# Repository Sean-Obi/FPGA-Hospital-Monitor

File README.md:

# FPGA Hospital Monitor

A three-channel patient monitor built on an FPGA: **ECG and heart rate**,
**blood oxygen (SpO₂)** and **skin temperature**, shown on a hospital-style
display.

The sensors are bought modules. Everything after them — the ADC control,
the I²C bus master, filtering, baseline removal, beat detection, the
heart-rate divider, the ratio-of-ratios oximetry maths, temperature
conversion, and the serial link — is Verilog running on a Digilent
Cmod A7-35T. The laptop only draws what it is sent.

The beat detector is scored against cardiologist annotations from the
PhysioNet MIT-BIH Arrhythmia Database, so its accuracy is a measured figure
rather than an impression.

> **Not a medical device.** Hobby and education only. Do not use it for
> diagnosis or treatment.

---

## The signal chain

```
 electrodes          fingertip             skin
     |                   |                   |
  AD8232             MAX30102              TMP36
  amp + filters      red + IR LEDs,        10 mV / °C
  (bought)           18-bit ADC (bought)   (bought)
     |                   |                   |
     |                   |             op-amp buffer     <- needed, see Wiring
     |                   |                   |
     v                   v                   v
   XADC VAUX4         I²C bus             XADC VAUX12
     |                   |                   |
 xadc_reader       i2c_master           xadc_reader
 (2 channels,      max30102_driver      (same block)
  sequencer)           |                     |
     |             spo2_calc             temp_convert
     |             udiv (44-bit)             |
     |                   |                   |
 ecg_filter              |                   |
 baseline_remove         |                   |
 beat_detect             |                   |
 bpm_calc / bpm_div      |                   |
     |                   |                   |
     +-------------------+-------------------+
                         |
                  telemetry_uart        S/B/T/O messages, 115200 baud
                         |
                  scripts/ecg_monitor.py --port COMx
```

`buzzer` and `led_flash` hang off the `beat` pulse.

---

## What goes over the serial line

Every message is six characters: a tag, four decimal digits with leading
zeros, newline.

| Message | Meaning | How often |
|---|---|---|
| `S2048` | one raw ECG sample, 0–4095 | 500 / s |
| `B0075` | heart rate, BPM | once per beat |
| `T0345` | skin temperature, tenths of °C (34.5 °C) | 2 / s |
| `O0098` | SpO₂ percent. `O0000` = no finger. `O0999` = MAX30102 not responding | every 2.6 s |

Bandwidth: the sample stream is 500 × 6 × 10 = 30,000 bit/s; the rest is a
few messages a second. About 27 % of the 115,200 baud line.

Measured on hardware: 0 bad lines in 114,000 messages.

---

## Hardware

| Part | Notes |
|---|---|
| Digilent Cmod A7-35T | 48-pin DIP, has the XADC built in |
| AD8232 breakout | ECG front end. Run it at **3.3 V**, not 5 V |
| ECG electrode pads + 3-lead snap cable | the cable plugs into the AD8232's 3.5 mm jack |
| MAX30102 module | pulse oximeter, I²C. **Pull-up jumper must be on 3.3 V** — see below |
| TMP36 | analogue temperature sensor, TO-92 |
| MCP6002 or LM358 | dual op-amp, used as a unity-gain buffer for the TMP36 |
| 0.1 µF capacitor | decoupling for the TMP36 |
| Piezo buzzer (passive) + 100–220 Ω resistor | a piezo draws well under 1 mA, so it runs straight off the FPGA pin |
| Full-size breadboard + male jumpers | the Cmod straddles the centre channel |

### The Cmod A7 pins this design uses

**Only two of the 48 DIP pins are power:** pin 24 (VU) and pin 25 (GND).
There is **no 3.3 V on the DIP header** — it is only on the Pmod socket.
With USB attached the board drives about 4.7 V *out* onto pin 24, which
would damage every sensor here. Power all three from Pmod JA pin 6 (or 12).

DIP pins 15 and 16 each pass through an on-board 2.32 kΩ / 1 kΩ divider,
so they accept **0 to 3.3 V** and present 0 to 1 V to the XADC. One ADC
count is therefore 3.32 V / 4096 = **0.81 mV** at the pin (measured: 4051
counts on the 3.28 V rail). The negative half of each pair (G2, J2) is
grounded on the board, so they are single-ended inputs. With nothing
connected, the 1 kΩ leg holds the pin at 0 V, so an unwired input reads 0.

### Wiring: AD8232 (ECG)

| AD8232 | Cmod A7 |
|---|---|
| 3.3V | Pmod JA pin 6 |
| GND | Pmod JA pin 5, or DIP pin 25 |
| OUTPUT | DIP pin 15 (`xa_p[0]`, package pin G3, VAUX4) |

Electrode cable into the 3.5 mm jack. IEC colours: **red** just below the
right collarbone, **yellow** just below the left collarbone, **green** on the
lower left ribs. On the soft flesh, not on the bone. If the R peak comes
out pointing down, swap red and yellow.

### Wiring: TMP36 (skin temperature) — needs the buffer

The TMP36 can only source **50 µA**. The Cmod's input divider draws about
**250 µA** at the voltages involved, so connected directly the sensor's
output collapses and the reading is garbage. A unity-gain op-amp buffer
in between fixes it: the op-amp copies the voltage and supplies the current.

```
   TMP36 (flat face towards you, legs down):   +Vs   Vout   GND

   +Vs  ─── Pmod JA 3.3 V        (0.1 µF from +Vs to GND, close to the sensor)
   GND  ─── GND
   Vout ─── op-amp IN+ (pin 3)

   MCP6002 / LM358, DIP-8, same pinout for both:
       pin 8  V+   ─── Pmod JA 3.3 V
       pin 4  V−   ─── GND
       pin 3  IN+  ─── TMP36 Vout
       pin 2  IN−  ─── pin 1   (output tied back to the inverting input = gain of 1)
       pin 1  OUT  ─── DIP pin 16  (`xa_p[1]`, package pin H2, VAUX12)
```

Tape the flat face of the TMP36 against skin with something over it to
insulate it from the air. Inner wrist works; armpit reads closer to core.
It reads **skin** temperature, typically 32–35 °C, and is labelled as such
on the display.

### Wiring: MAX30102 (SpO₂)

| MAX30102 | Cmod A7 |
|---|---|
| VIN | Pmod JA 3.3 V |
| GND | GND |
| SCL | DIP pin 2 (`scl`, package pin L3) |
| SDA | DIP pin 3 (`sda`, package pin A16) |
| INT | not used |

**Check the pull-up jumper.** Most of these modules have a three-pad
solder jumper that selects whether the I²C pull-ups go to 1.8 V or 3.3 V.
The FPGA's inputs need 2.0 V to read a logic high, so at 1.8 V nothing
works and nothing explains why. With the module powered, a multimeter from
SCL to GND must read about 3.3 V. If it reads 1.8 V, move the jumper, or
add 4.7 kΩ resistors from SCL and SDA to 3.3 V. The MAX30102's own pins are
rated to 6 V, so 3.3 V pull-ups are fine for it.

Finger on the sensor window, light pressure, keep still. The first reading
takes about 5 s (two 2.56 s blocks).

### Buzzer

DIP pin 1 (`piezo`, package pin M3) → 100–220 Ω → buzzer **+**. Buzzer **−** to GND.

### Safety

Electrodes on your chest is a different risk category from a sensor
clipped on a finger.

- **Unplug the laptop charger while electrodes are attached.** USB to a
  mains-powered laptop puts you indirectly on mains equipment. Laptop on
  battery, board on USB.
- Use proper single-use ECG pads.
- **Do not power the board from batteries on DIP pin 24 while USB is
  connected.** The reference manual is explicit — "if you have a power
  source attached to the VU pin, you must disconnect it before attaching
  a USB host, or risk damaging it." Since USB carries the data, battery
  power is not an option for this project.
- Insert and remove the Cmod with USB unplugged. Nothing is live until
  USB goes in.

---

## The shield PCB (KiCad)

The breadboard works for bring-up, but three sensor modules, an op-amp and
a regulator on jumper wires is fragile and noisy. `hardware/` holds a KiCad
design for a shield the Cmod A7 plugs into, with everything else soldered
on. Two-layer, 80 × 75 mm, through-hole throughout so it can be built with
an iron.

What is on it, and why:

| Ref | Part | Why |
|---|---|---|
| U3 | Cmod A7 socket, 2 × 24-pin female header, 0.6 in apart | the FPGA plugs in from above |
| U2, C1, C2 | MCP1700-3302 LDO, 2 × 1 µF | makes 3.3 V from VU (DIP pin 24, ~4.7 V), so no flying lead from the Pmod socket |
| J1 | 1 × 6 socket | the AD8232 breakout plugs in |
| J2 | 1 × 7 socket | the MAX30102 module plugs in |
| J3 | 1 × 3 socket | the TMP36 on a short lead, so it can be taped to skin |
| U1, C4 | MCP6002 dual op-amp, 100 nF | unity-gain buffer for the TMP36 (50 µA source limit vs the Cmod's 250 µA input divider); the spare half is tied off |
| C3 | 100 nF | decoupling at the TMP36 supply, as its datasheet asks |
| R1, BZ1 | 150 Ω, piezo buzzer | beat beep; the resistor keeps the FPGA pin under its 12 mA rating |
| H1–H4 | M3 holes | so it can be stood off a desk or screwed into a case |

The analogue inputs stay single-ended into DIP pins 15 and 16, as on the
breadboard — the Cmod's own dividers do the scaling — so the Verilog needs
no change to run on the shield.

## How the numbers are worked out

### Heart rate

An 8-point moving average, baseline subtraction, then a threshold
crossing with a 250 ms refractory window so the T wave cannot be counted
as a second beat. The gap between beats in samples goes into a sequential
divider: BPM = 30000 / period.

### Temperature (fixed point, no floating point)

TMP36: 500 mV at 0 °C, 10 mV per °C — so **tenths of a degree = mV − 500**.
Pin: 0.8105 mV per count, written as **830 / 1024**. 256 readings are
summed and the maths is done on the sum, keeping the fractional part of the
average:

```
tenths = ((sum × 830) >> (10 + 8)) − 500
```

One ADC count is 0.08 °C; averaging 256 gives roughly 0.005 °C resolution.
A new value every 0.5 s. (`rtl/temp_convert.v`)

### SpO₂ (ratio of ratios)

Each light reading is a steady level (DC: tissue) plus a small wobble (AC:
blood pulsing). Oxygenated blood absorbs infrared more than red, so

```
       (AC_red / DC_red)
  R = -------------------          SpO₂ ≈ 110 − 25 R       (textbook linear fit)
       (AC_ir  / DC_ir)
```

Per block of 256 samples (2.56 s at 100 sps) and per colour: DC = sum >> 8,
AC = max − min. Then one 44-bit sequential division gives R scaled by 100,
and because 25/100 = 1/4:

```
  R100 = (AC_red × DC_ir × 100) / (DC_red × AC_ir)
  SpO₂ = (442 − R100) >> 2,  clamped to 0..100
```

"No finger" is an IR DC level below 30,000 counts. The linear fit is the
usual learning approximation; real oximeters use a curve calibrated on
volunteers. (`rtl/spo2_calc.v`, `rtl/udiv.v`)

### The MAX30102 driver

Bus recovery (9 clocks + STOP), software reset, read `PART_ID` (must be
0x15), configure — FIFO, ADC range 4096 nA, 100 sps, 411 µs pulses
(18-bit), both LEDs 6.2 mA, clear pointers, **mode last** — then poll the
FIFO write/read pointers every 2 ms and read six bytes per waiting sample.
Any NACK, wrong ID or stuck clock drops `sensor_ok`, waits a second and
starts again, so an unplugged sensor shows `ERR` rather than hanging.
(`rtl/max30102_driver.v`, `rtl/i2c_master.v`)

### Two ADC channels on one XADC

The XADC runs in continuous-sequence mode over VAUX4 and VAUX12. At each
end-of-conversion the channel number is latched and that channel's result
register is read over the DRP one clock later, so the two never get mixed
up. Both are then released together at 500 Hz. (`rtl/xadc_reader.v`)

---

## Software

| Tool | For |
|---|---|
| Vivado (free Standard edition) | building the bitstream |
| Icarus Verilog + GTKWave | simulation |
| Python 3.12 + `pyserial`, `pyqtgraph`, `PyQt6`, `numpy` | the live monitor |
| `wfdb`, `scipy` | PhysioNet playback and validation |

```
py -3.12 -m venv .venv312
.\.venv312\Scripts\Activate.ps1
python -m pip install pyserial pyqtgraph PyQt6 numpy wfdb scipy
```

Python 3.12, not 3.14: PyQt6 has no pre-built wheels for 3.14 yet and pip
will try to compile it and fail looking for `qmake`.

---

## Simulating (no board needed)

```
python scripts/run_all_sims.py
```

Builds and runs all 19 testbenches, about 70 seconds. Run it after
changing anything in `rtl/`. The top-level test feeds a synthetic ECG into
the XADC model, a synthetic pulse into the MAX30102 model, a known code
into the temperature channel, and decodes the serial line bit by bit like
the laptop would: 75 BPM, 35.0 °C and 98 % must all come out, then 0 with
the finger off and 999 with the oximeter unplugged.

| Testbench | Checks |
|---|---|
| `i2c_master_tb` | write/read with repeated START, auto-increment, NACK from an absent slave, stuck-SCL recovery |
| `max30102_driver_tb` | reset once, registers exactly as configured, mode written last, every sample delivered once, recovery when the sensor appears, wrong PART_ID rejected |
| `spo2_calc_tb` | exact DC/AC from known blocks; R = 0.5 → 98 %, 1.0 → 85 %, clamps, no finger, flat line, no divide-by-zero |
| `temp_convert_tb` | 617 → 0.0 °C, 1049 → 35.0 °C, clamps, averaging |
| `udiv_tb` | against Verilog's own `/`, including the widest SpO₂ operands and ÷0 |
| `xadc_reader_tb` | two channels never cross, every DRP read asks for the right register |
| `telemetry_uart_tb` | all four messages, priority order, nothing dropped at 500 Hz, same-clock collision |

Two stand-ins live in `tb/` and **must never be added to Vivado**:
`xadc_model.v` defines a module called `XADC` and would shadow the real
hardware block; `max30102_model.v` is the oximeter chip seen from its I²C
pins.

Each testbench was checked by deliberately breaking the module it tests
(swapped channels, inverted ACK, wrong byte order, reading the FIFO
unconditionally) and confirming the test failed.

To look at one in detail:

```
iverilog -g2012 -o build/top_sim tb/top_tb.v tb/xadc_model.v tb/max30102_model.v rtl/*.v
vvp build/top_sim
gtkwave top_tb.vcd
```

---

## Building for the board

1. New Vivado RTL project, part **xc7a35tcpg236-1** (or the Cmod A7-35T
   board file from the Xilinx Board Store).
2. Add every file in `rtl/`. Do **not** add anything from `tb/` or
   `practice/`.
3. Add `constraints/ecg_monitor.xdc` only. `Cmod-A7-Master.xdc` is kept
   for reference and is fully commented out, but there is no reason to add it.
4. Set `top` as the top module.
5. Generate Bitstream.
6. Open Hardware Manager → Open Target → Auto Connect, then **right-click
   `xc7a35t_0` → Program Device → Program**.

Step 6 is the one that gets missed. Setting the bitstream file and seeing
"Programmed" in the status column does **not** mean your design is loaded:
that column reflects the DONE pin, which is also high when the board boots
its factory demo from flash. The Tcl console must show
`program_hw_devices`. Programming is volatile — unplugging USB wipes it.

Vivado 2025.2 installs to `C:\AMDDesignTools\`, not `C:\Xilinx\`.

---

## Bring-up, in order

Each step assumes the one before it worked, so a failure tells you where
the problem is. The numbers are what this board measured.

**1. Does it run at all?** LD2 (`led[1]`) blinks at about 1.4 Hz. It
depends on nothing but the clock: if it blinks, the bitstream loaded, the
clock arrives and the pin constraints are right. LD0 (the RGB LED) stays
dark — if it is cycling colours you are running the factory demo, not this.

**2. Is the serial line working?**

```
python scripts/ecg_serial_monitor.py --list-ports
python scripts/ecg_serial_monitor.py --port COM4 --dump
```

Measured: 495–504 Hz (the wobble is Python's `sleep`, not the FPGA),
0 bad lines. With nothing on the analogue pin the samples read 0 or 1 —
the on-board divider holds it at ground, and the ±1 flicker is the ADC's
last bit, which is proof it is converting rather than frozen.

**3. Does the analogue input read a voltage?** One jumper from Pmod JA
pin 6 (3.3 V) to the breadboard row of DIP pin 15. Measured: **4051
counts**, i.e. 3.28 V — correct, and usefully *not* saturated at 4095, so
the gain is confirmed, not just the direction. Remove the jumper.

**4. Is the AD8232 alive?** Wire it (power + OUTPUT, no electrodes).
Measured: **2023–2030 counts** = 1.64 V, exactly half the 3.28 V rail,
with the same ±3 count noise as the bare pin.

**5. Electrodes on.** `python scripts/ecg_serial_monitor.py --port COM4`
— or the terminal plotter `python scripts/ascii_scope.py COM4` if the GUI
is not installed yet. You are looking for a recognisable trace.

Two tells that the electrodes are *not* connected to you, both seen on
this board before the pads were seated: peak-to-peak under ~50 counts of
structureless noise, and essentially **zero 50 Hz pickup** — a pad on skin
always picks up some mains hum, so silence at 50 Hz means an open
circuit. Pressing on the pads and tugging the leads should throw the trace
around; if it stays flat, the input is open. Check the 3.5 mm plug clicks
home, the snap studs are latched, the gel is moist (a drop of water
revives it), and the pads are on bare skin.

**6. Set the threshold.** Capture ten seconds with the pads on:

```
python -c "import serial,os; s=serial.Serial('COM4',115200,timeout=2); f=open('capture.txt','w'); [f.write(s.readline().decode(errors='replace')) for _ in range(5000)]; f.close(); print(os.path.getsize('capture.txt'))"
```

Read the R-peak height above baseline off it. `THRESHOLD` in `rtl/top.v`
should sit between the T wave and the R peak, roughly 40–50 % of the R
height. The default of 70 (57 mV at the AD8232 output) was chosen on a
simulated waveform; on the first real recording it caught roughly every
other beat, so it is likely too high. The validation sweep below is the
honest way to pick it.

**7. Temperature and SpO₂.** Wire the TMP36 (through the buffer) and the
MAX30102. `--dump` shows both:

```
   4478 samples    500.6 Hz   BPM  72   SpO2  98   temp  34.5 C   bad lines 0
```

`SpO2 ERR` = the MAX30102 is not acknowledging: check the jumper (step
above), SCL/SDA not swapped, 3.3 V on VIN. `SpO2 --` = no finger, or not
enough light coming back (press a little more firmly).

**8. The display.**

```
python scripts/ecg_monitor.py --port COM4
```

Buzzer and LD1 follow your pulse.

---

## Validation against PhysioNet

This is what makes the accuracy figure meaningful, and it needs no
hardware.

```
python scripts/make_ecg_hex.py --record 100 --seconds 60

iverilog -g2012 -o build/val_sim tb/validation_tb.v \
         rtl/heart_pipeline.v rtl/ecg_filter.v rtl/baseline_remove.v \
         rtl/beat_detect.v rtl/bpm_calc.v rtl/bpm_div.v \
         rtl/bpm_uart.v rtl/uart.v

vvp build/val_sim +samples=data/100_samples.hex +count=30000

python scripts/score_detection.py --record 100
```

Reports sensitivity, PPV and F1 against the cardiologist markings.

To choose the threshold from measurements rather than by eye:

```
python scripts/score_detection.py --record 100 --sweep 50 400 25
```

That rebuilds and re-runs at each threshold and prints a table.

No internet? `python scripts/make_ecg_hex.py --synthetic` makes a file
with the same layout so the flow can be tested offline. It is not a
substitute for real data.

---

## Known limitations

- The analogue front ends are bought modules; this project is about the
  digital design, not analogue circuit design.
- Single ECG lead.
- SpO₂ uses the linear 110 − 25R fit, not a calibrated curve, and reports
  on 2.56 s blocks with no outlier rejection. Motion ruins it, as it does
  on real oximeters.
- Temperature is skin temperature, not core.
- No leads-off detection on the ECG; the AD8232 provides `LO+`/`LO−` but
  nothing reads them.
- `xadc_reader` and `max30102_driver` are verified against behavioural
  models, not against silicon. The XADC sequencer configuration and the
  MAX30102 register values are the least-tested parts of the design.
- The shield PCB is designed and DRC-clean but has not been fabricated;
  every hardware measurement here is from the breadboard.

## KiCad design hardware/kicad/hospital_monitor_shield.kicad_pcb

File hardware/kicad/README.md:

# KiCad files

Open `hospital_monitor_shield.kicad_pro` in KiCad 7 or later.

| File | What |
|---|---|
| `hospital_monitor_shield.kicad_sch` | the schematic |
| `hospital_monitor_shield.kicad_pcb` | the board, routed, with a ground pour on the back |
| `ECG.pretty/CmodA7_DIP48.kicad_mod` | footprint for the Cmod A7 socket (two 1x24 female headers, 0.6 in apart) |
| `fp-lib-table` | tells KiCad where that footprint library is |

Both files are generated by the scripts in `../tools/` from a single
description, so the schematic and board cannot drift apart:

```
python hardware/tools/make_schematic.py
kicad-cli sch export netlist --format kicadsexpr -o build/shield.net hardware/kicad/hospital_monitor_shield.kicad_sch
python hardware/tools/make_pcb.py build/shield.net          # placement, rules, outline -> .kicad_pcb + .dsn
java -jar freerouting.jar -de build/shield.dsn -do build/shield.ses -mp 50
python hardware/tools/finish_pcb.py build/shield.ses        # tracks in, ground pour, DRC-ready
python hardware/tools/render_pcb.py                         # the green renders in ../images
```

The library symbols and footprints are copied into the files, so they
open without any extra libraries installed.

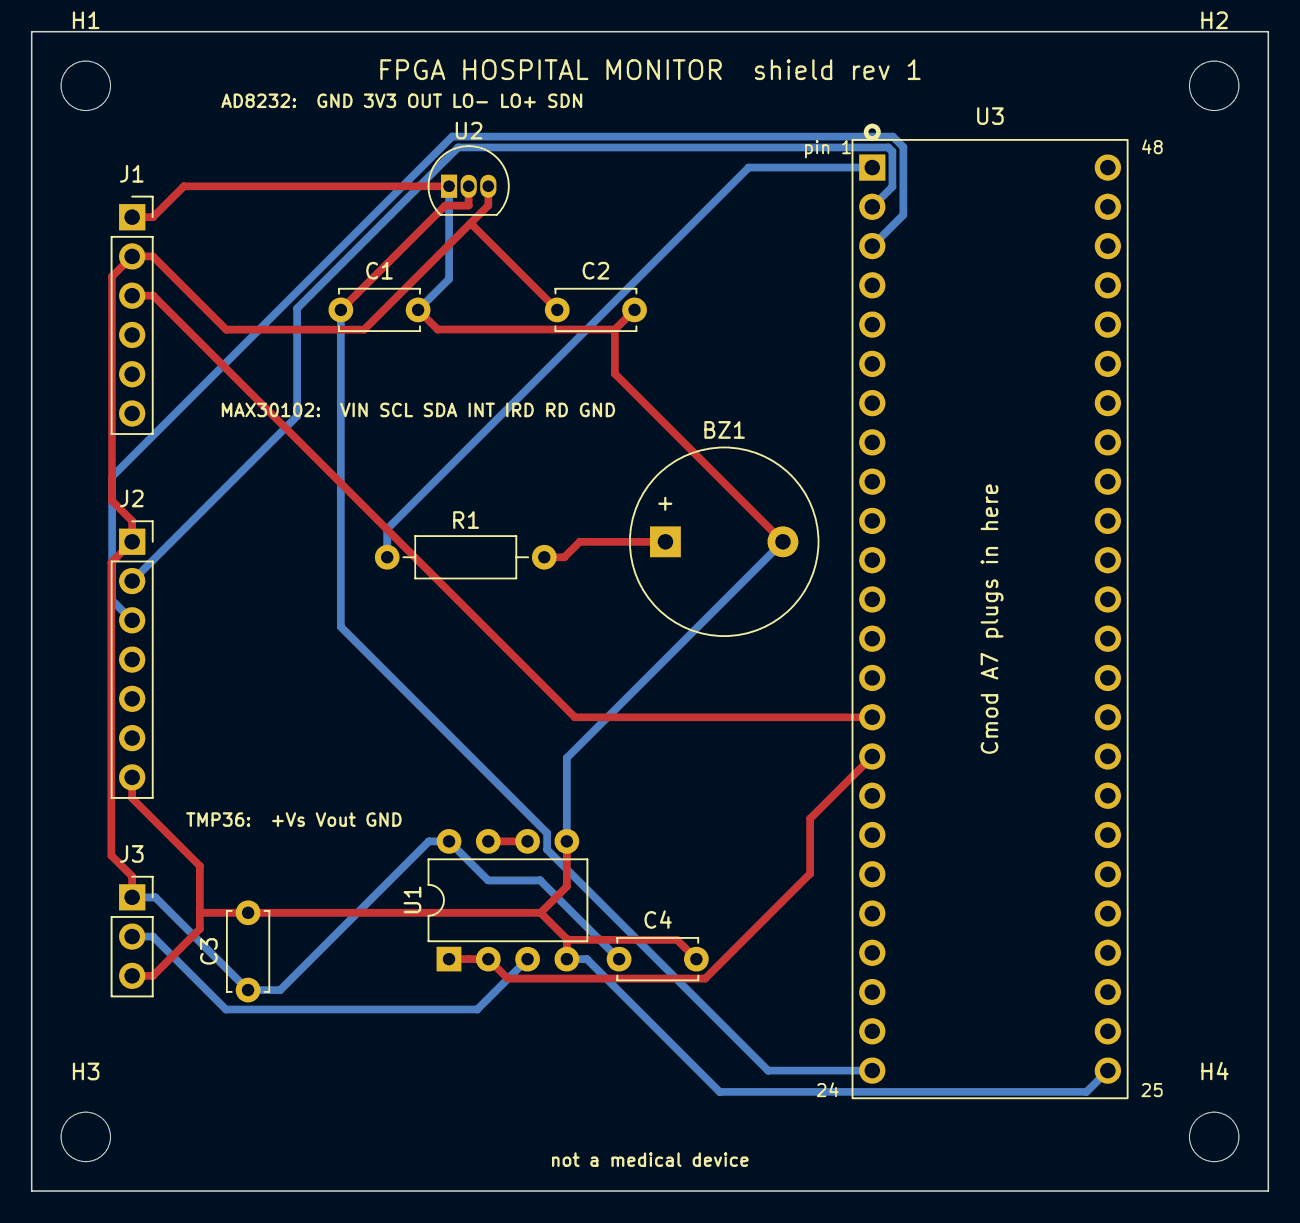
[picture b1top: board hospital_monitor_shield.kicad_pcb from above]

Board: 2 copper layers, 80.0 x 75.0 mm, 16 parts (0 on the bottom side), 11 nets.

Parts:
BZ1: passive buzzer; Buzzer_12x9.5RM7.6
C1, C2: 1u; C_Disc_D5.0mm_W2.5mm_P5.00mm
C3, C4: 100n; C_Disc_D5.0mm_W2.5mm_P5.00mm
H1, H2, H3, H4: M3; MountingHole_3.2mm_M3
J1: AD8232 ECG breakout; PinSocket_1x06_P2.54mm_Vertical
J2: MAX30102 oximeter module; PinSocket_1x07_P2.54mm_Vertical
J3: TMP36 on leads; PinSocket_1x03_P2.54mm_Vertical
R1: 150; R_Axial_DIN0207_L6.3mm_D2.5mm_P10.16mm_Horizontal
U1: MCP6002; DIP-8_W7.62mm
U2: MCP1700-3302; TO-92_Inline
U3: Cmod A7-35T; CmodA7_DIP48

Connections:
+3V3: C2.1, C3.1, C4.1, J1.2, J2.1, J3.1, U1.8, U2.3
/BUZZER: R1.1, U3.1
/ECG: J1.3, U3.15
/SCL: J2.2, U3.2
/SDA: J2.3, U3.3
/TEMP: U1.1, U1.2, U3.16
/VU: C1.1, U2.2, U3.24
GND: BZ1.2, C1.2, C2.2, C3.2, C4.2, J1.1, J2.7, J3.3, U1.4, U1.5, U2.1, U3.25
unnamed: BZ1.1, R1.2
unnamed: J3.2, U1.3
unnamed: U1.6, U1.7
